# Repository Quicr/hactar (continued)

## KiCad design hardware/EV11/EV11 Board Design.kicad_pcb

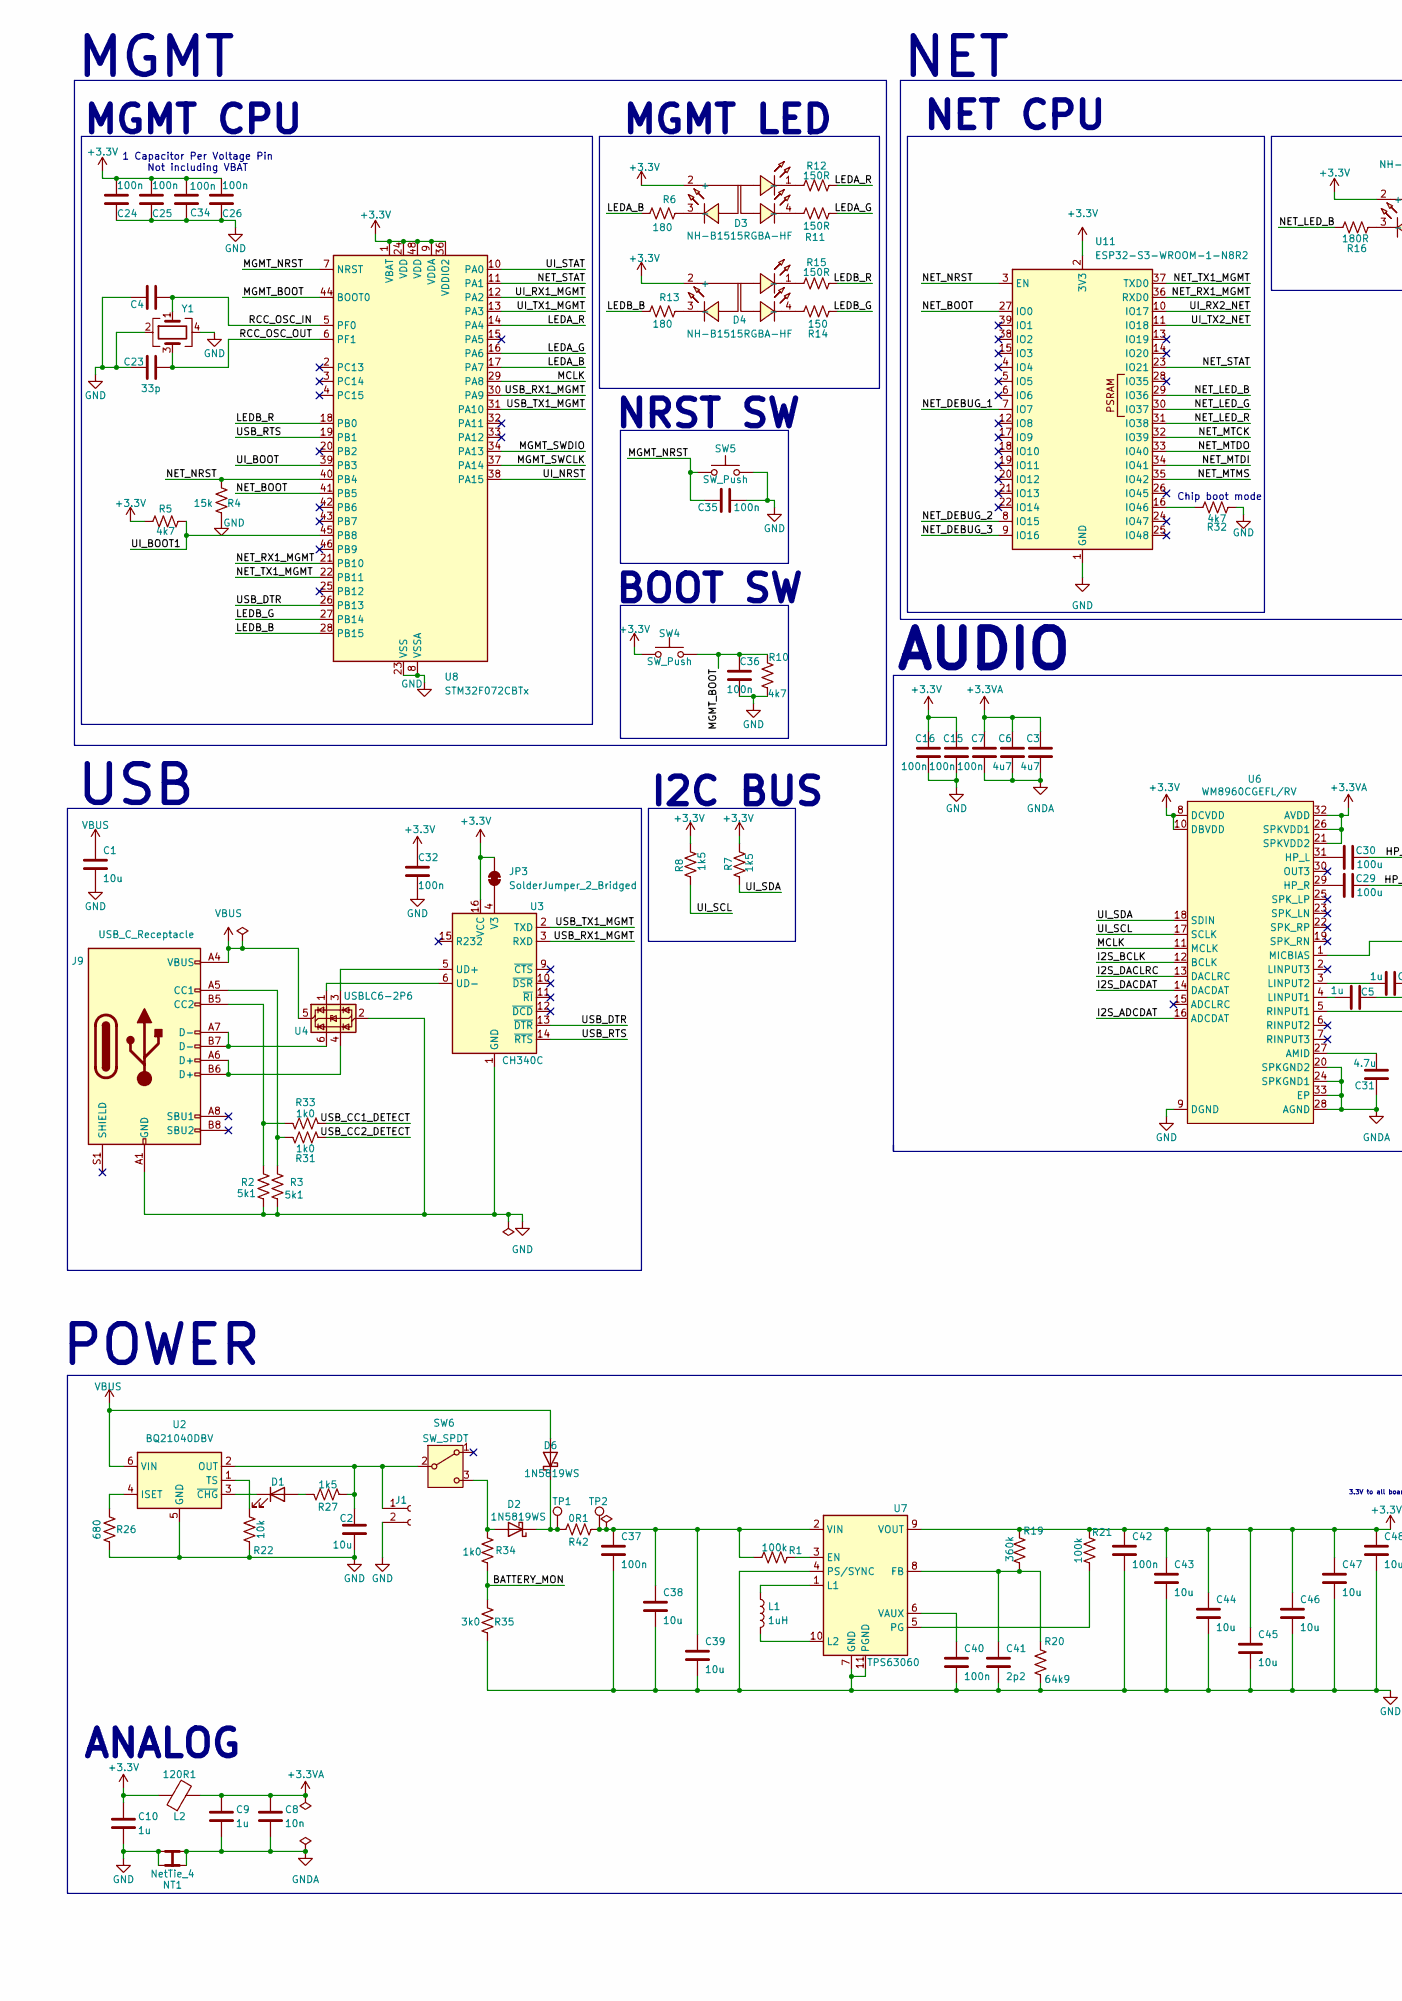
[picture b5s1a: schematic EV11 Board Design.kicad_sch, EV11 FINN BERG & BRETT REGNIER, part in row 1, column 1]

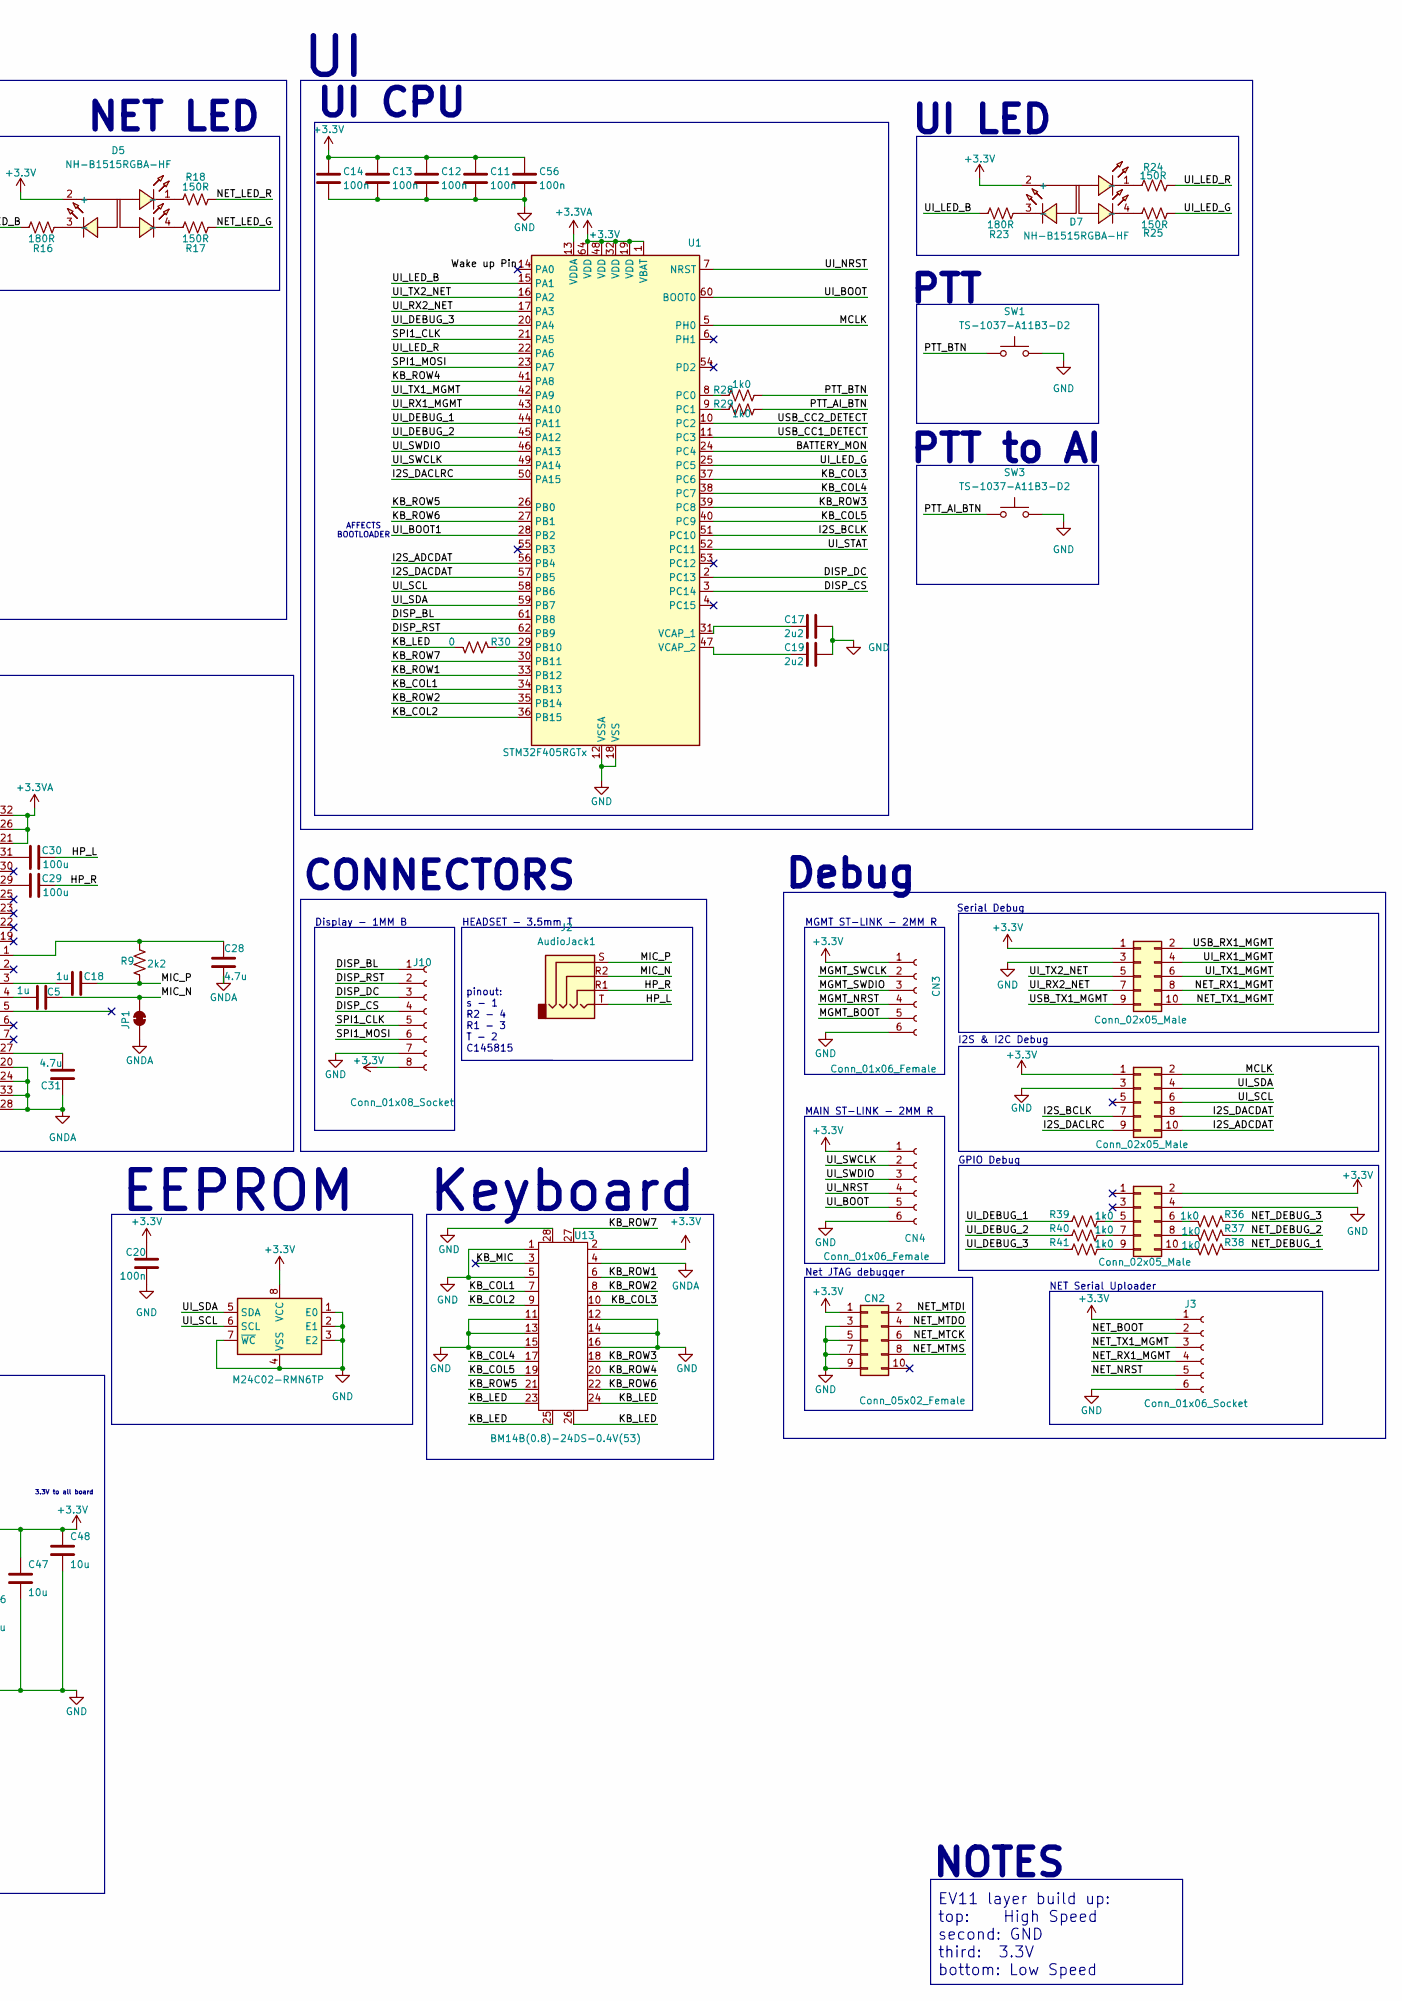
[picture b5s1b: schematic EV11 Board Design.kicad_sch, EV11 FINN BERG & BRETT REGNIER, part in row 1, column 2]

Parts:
C1, C2: 10u; C_0402_1005Metric; JLCPCB Part # C307415
C3, C6: 4u7; C_0402_1005Metric; JLCPCB Part # C23733
C4, C23: 33p; C_0805_2012Metric; JLCPCB Part # C107115
C5, C9, C10, C18: 1u; C_0402_1005Metric; JLCPCB Part # C52923
C7, C11, C12, C13, C14, C15, C16, C20, C24, C25, C26, C32, C34, C35, C36, C56: 100n; C_0402_1005Metric; JLCPCB Part # C1525
C8: 10n; C_0402_1005Metric; JLCPCB Part # C15195
C17, C19: 2u2; C_0402_1005Metric; JLCPCB Part # C12530
C28, C31: 4.7u; C_0402_1005Metric; JLCPCB Part # C23733
C29, C30: 100u; C_1206_3216Metric; JLCPCB Part # C15008
C37, C40, C42: 100n; C_0805_2012Metric; JLCPCB Part # C495959
C38, C39, C43, C44, C45, C46, C47, C48: 10u; C_0805_2012Metric; JLCPCB Part # C83061
C41: 2p2; C_0805_2012Metric; JLCPCB Part # C519933
CN2: Conn_05x02_Female; IDC-SMD_10P-P1.27_X1270WVS-2X05B-6TV01; JLCPCB Part # C2962219
CN3, CN4: Conn_01x06_Female; JST_SH_BM06B-SRSS-TB_1x06-1MP_P1.00mm_Vertical; JLCPCB Part # C3029336
CN5, CN6, CN7: Conn_02x05_Male; IDC-SMD_10P-P1.27_X1270WVS-2X05B-6TV01; JLCPCB Part # C2962219
D1: LED; D_0805_2012Metric; JLCPCB Part # C130114
D2, D6: 1N5819WS; D_SOD-323; JLCPCB Part # C191023
D3, D4, D5, D7: NH-B1515RGBA-HF; LED-ARRAY-SMD_4P-L1.6-W1.5-TL_NH-B1515RGBA; JLCPCB Part # C2874115
J1: Conn_01x02_Socket; JST_PH_S2B-PH-SM4-TB_1x02-1MP_P2.00mm_Horizontal; JLCPCB Part # C295747
J2: AudioJack1; Jack_3.5mm_PJ320D_Horizontal; MPN PJ-320D; JLCPCB Part # C431535
J3: Conn_01x06_Socket; JST_SH_BM06B-SRSS-TB_1x06-1MP_P1.00mm_Vertical; JLCPCB Part # C3029336
J9: USB_C_Receptacle; USB_C_Receptacle_HRO_TYPE-C-31-M-12; JLCPCB Part # C165948
J10: Conn_01x08_Socket; JST_SHL_SM08B-SHLS-TF_1x08-1MP_P1.00mm_Horizontal; JLCPCB Part # C3029347
JP1: SolderJumper_2_Bridged; NetTie-2_SMD_Pad0.5mm
JP3: SolderJumper_2_Bridged; SolderJumper-2_P1.3mm_Bridged_RoundedPad1.0x1.5mm
L1: 1uH; MCL2016A1R0MT; JLCPCB Part # C370013
L2: 120R1; L_0603_1608Metric; JLCPCB Part # C127301
NT1: NetTie_4; NetTie-4_SMD_Pad0.5mm
R1, R21: 100k; R_0402_1005Metric; JLCPCB Part # C25741
R2, R3: 5k1; R_0402_1005Metric; JLCPCB Part # C25905
R4: 15k; R_0402_1005Metric; JLCPCB Part # C25756
R5, R10, R32: 4k7; R_0402_1005Metric; JLCPCB Part # C25900
R6, R13: 180; R_0402_1005Metric; JLCPCB Part # C25087
R7, R8, R27: 1k5; R_0402_1005Metric; JLCPCB Part # C25867
R9: 2k2; R_0402_1005Metric; JLCPCB Part # C25879
R11, R12, R15, R17, R18, R24, R25: 150R; R_0402_1005Metric; JLCPCB Part # C25082
R14: 150; R_0402_1005Metric; JLCPCB Part # C25082
R16, R23: 180R; R_0402_1005Metric; JLCPCB Part # C25087
R19: 360k; R_0402_1005Metric; JLCPCB Part # C45956
R20: 64k9; R_0402_1005Metric; JLCPCB Part # C26984
R22: 10k; R_0402_1005Metric; JLCPCB Part # C25744
R26: 680; R_0402_1005Metric; JLCPCB Part # C25130
R28, R29, R31, R33, R34, R36, R37, R38, R39, R40, R41: 1k0; R_0402_1005Metric; JLCPCB Part # C11702
R30: 0; R_0402_1005Metric; JLCPCB Part # C17168
R35: 3k0; R_0402_1005Metric; JLCPCB Part # C25784
R42: 0R1; R_0603_1608Metric
SW1, SW3: TS-1037-A11B3-D2; KEY-SMD_2P-L7.1-W10.6-P4.00-LS9.0; JLCPCB Part # C499331
SW4, SW5: SW_Push; SW_DIP_SPSTx01_Slide_6.7x4.1mm_W6.73mm_P2.54mm_LowProfile_J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; JLCPCB Part # C266189
SW6: SW_SPDT; SW-TH_SS-12D11G5R; JLCPCB Part # C388633
TP1, TP2: TestPoint; TestPoint_THTPad_D1.5mm_Drill0.7mm
U1: STM32F405RGTx; LQFP-64_10x10mm_P0.5mm; JLCPCB Part # C15742
U2: BQ21040DBV; SOT-23-6
U3: CH340C; SOIC-16_3.9x9.9mm_P1.27mm; JLCPCB Part # C84681
U4: USBLC6-2P6; SOT-666; JLCPCB Part # C2827693
U5: M24C02-RMN6TP; SOIC-8_3.9x4.9mm_P1.27mm; JLCPCB Part # C83836
U6: WM8960CGEFL/RV; QFN-32-1EP_5x5mm_P0.5mm_EP3.45x3.45mm_ThermalVias; JLCPCB Part # C18752
U7: TPS63060; Texas_S-PWSON-N10_ThermalVias; JLCPCB Part # C48567
U8: STM32F072CBTx; LQFP-48_7x7mm_P0.5mm; JLCPCB Part # C80488
U11: ESP32-S3-WROOM-1-N8R2; ESP32-S3-WROOM-1U; JLCPCB Part # C3013944
U13: BM14B(0.8)-24DS-0.4V(53); BM14B(0.B)-24DS-0.4V(53); JLCPCB Part # C9900001863
Y1: Crystal_GND24; Crystal_SMD_3225-4Pin_3.2x2.5mm; JLCPCB Part # C13738

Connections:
+3.3V: C10.1, C11.1, C12.1, C13.1, C14.1, C15.2, C16.2, C20.2, C24.2, C25.2, C26.2, C32.1, C34.2, C42.1, C43.1, C44.1, C45.1, C46.1, C47.1, C48.1, C56.1, CN2.1, CN3.1, CN4.1, CN5.1, CN6.1, CN7.2, D3.2 (+), D4.2 (+), D5.2 (+), D7.2 (+), J3.1, J10.8, JP3.2 (B), L2.1, R5.1, R7.1, R8.1, R19.2, R21.2, SW4.1, U1.1 (VBAT), U1.19 (VDD), U1.32 (VDD), U1.48 (VDD), U1.64 (VDD), U3.16 (VCC), U5.8 (VCC), U6.8 (DCVDD), U6.10 (DBVDD), U7.9 (VOUT), U8.1 (VBAT), U8.9 (VDDA), U8.24 (VDD), U8.36 (VDDIO2), U8.48 (VDD), U11.2 (3V3), U13.2
+3.3VA: C3.1, C6.1, C7.2, C8.1, C9.1, L2.2, U1.13 (VDDA), U6.21 (SPKVDD2), U6.26 (SPKVDD1), U6.32 (AVDD)
/BATTERY_MON: R34.1, R35.2, U1.24 (PC4)
/DISP_BL: J10.1, U1.61 (PB8)
/DISP_CS: J10.4, U1.3 (PC14)
/DISP_DC: J10.3, U1.2 (PC13)
/DISP_RST: J10.2, U1.62 (PB9)
/HP_L: C30.2, J2.T
/HP_R: C29.2, J2.R1
/I2S_ADCDAT: CN5.10, U1.56 (PB4), U6.16 (ADCDAT)
/I2S_BCLK: CN5.7, U1.51 (PC10), U6.12 (BCLK)
/I2S_DACDAT: CN5.8, U1.57 (PB5), U6.14 (DACDAT)
/I2S_DACLRC: CN5.9, U1.50 (PA15), U6.13 (DACLRC)
/KB_COL1: U1.34 (PB13), U13.7
/KB_COL2: U1.36 (PB15), U13.9
/KB_COL3: U1.37 (PC6), U13.10
/KB_COL4: U1.38 (PC7), U13.17
/KB_COL5: U1.40 (PC9), U13.19
/KB_LED: R30.2, U13.23, U13.24, U13.25, U13.26
/KB_MIC: U13.3
/KB_ROW1: U1.33 (PB12), U13.6
/KB_ROW2: U1.35 (PB14), U13.8
/KB_ROW3: U1.39 (PC8), U13.18
/KB_ROW4: U1.41 (PA8), U13.20
/KB_ROW5: U1.26 (PB0), U13.21
/KB_ROW6: U1.27 (PB1), U13.22
/KB_ROW7: U1.30 (PB11), U13.27
/LEDA_B: R6.2, U8.17 (PA7)
/LEDA_G: R11.2, U8.16 (PA6)
/LEDA_R: R12.2, U8.14 (PA4)
/LEDB_B: R13.2, U8.28 (PB15)
/LEDB_G: R14.2, U8.27 (PB14)
/LEDB_R: R15.2, U8.18 (PB0)
/MCLK: CN5.2, U1.5 (PH0), U6.11 (MCLK), U8.29 (PA8)
/MGMT_BOOT: C36.2, CN3.5, R10.2, SW4.2, U8.44 (BOOT0)
/MGMT_NRST: C35.1, CN3.4, SW5.2, U8.7 (NRST)
/MGMT_SWCLK: CN3.2, U8.37 (PA14)
/MGMT_SWDIO: CN3.3, U8.34 (PA13)
/MIC_N: C5.2, J2.R2, JP1.1 (A)
/MIC_P: C18.2, J2.S, R9.1
/NET_BOOT: J3.2, U8.41 (PB5), U11.27 (IO0)
/NET_DEBUG_1: R38.1, U11.7 (IO7)
/NET_DEBUG_2: R37.1, U11.8 (IO15)
/NET_DEBUG_3: R36.1, U11.9 (IO16)
/NET_LED_B: R16.1, U11.29 (IO36)
/NET_LED_G: R17.1, U11.30 (IO37)
/NET_LED_R: R18.1, U11.31 (IO38)
/NET_MTCK: CN2.6, U11.32 (IO39)
/NET_MTDI: CN2.2, U11.34 (IO41)
/NET_MTDO: CN2.4, U11.33 (IO40)
/NET_MTMS: CN2.8, U11.35 (IO42)
/NET_NRST: J3.5, R4.1, U8.40 (PB4), U11.3 (EN)
/NET_RX1_MGMT: CN6.8, J3.4, U8.21 (PB10), U11.36 (RXD0)
/NET_STAT: U8.11 (PA1), U11.23 (IO21)
/NET_TX1_MGMT: CN6.10, J3.3, U8.22 (PB11), U11.37 (TXD0)
/PTT_AI_BTN: R29.2, SW3.1
/PTT_BTN: R28.2, SW1.1
/RCC_OSC_IN: C4.2, U8.5 (PF0), Y1.1
/RCC_OSC_OUT: C23.2, U8.6 (PF1), Y1.3
/SPI1_CLK: J10.5, U1.21 (PA5)
/SPI1_MOSI: J10.6, U1.23 (PA7)
/UI_BOOT: CN4.5, U1.60 (BOOT0), U8.39 (PB3)
/UI_BOOT1: R5.2, U1.28 (PB2), U8.45 (PB8)
/UI_DEBUG_1: R39.1, U1.44 (PA11)
/UI_DEBUG_2: R40.1, U1.45 (PA12)
/UI_DEBUG_3: R41.1, U1.20 (PA4)
/UI_LED_B: R23.1, U1.15 (PA1)
/UI_LED_G: R25.1, U1.25 (PC5)
/UI_LED_R: R24.1, U1.22 (PA6)
/UI_NRST: CN4.4, U1.7 (NRST), U8.38 (PA15)
/UI_RX1_MGMT: CN6.4, U1.43 (PA10), U8.12 (PA2)
/UI_RX2_NET: CN6.7, U1.17 (PA3), U11.10 (IO17)
/UI_SCL: CN5.6, R8.2, U1.58 (PB6), U5.6 (SCL), U6.17 (SCLK)
/UI_SDA: CN5.4, R7.2, U1.59 (PB7), U5.5 (SDA), U6.18 (SDIN)
/UI_STAT: U1.52 (PC11), U8.10 (PA0)
/UI_SWCLK: CN4.2, U1.49 (PA14)
/UI_SWDIO: CN4.3, U1.46 (PA13)
/UI_TX1_MGMT: CN6.6, U1.42 (PA9), U8.13 (PA3)
/UI_TX2_NET: CN6.5, U1.16 (PA2), U11.11 (IO18)
/USB_CC1_DETECT: R33.1, U1.11 (PC3)
/USB_CC2_DETECT: R31.1, U1.10 (PC2)
/USB_DTR: U3.13 (~DTR), U8.26 (PB13)
/USB_RTS: U3.14 (~RTS), U8.19 (PB1)
/USB_RX1_MGMT: CN6.2, U3.3 (RXD), U8.30 (PA9)
/USB_TX1_MGMT: CN6.9, U3.2 (TXD), U8.31 (PA10)
/Wake up Pin: U1.14 (PA0)
GND: C1.2, C2.2, C4.1, C10.2, C11.2, C12.2, C13.2, C14.2, C15.1, C16.1, C17.1, C19.1, C20.1, C23.1, C24.1, C25.1, C26.1, C32.2, C34.1, C35.2, C36.1, C37.2, C38.2, C39.2, C40.2, C41.2, C42.2, C43.2, C44.2, C45.2, C46.2, C47.2, C48.2, C56.2, CN2.3, CN2.5, CN2.7, CN2.9, CN3.6, CN4.6, CN5.3, CN6.3, CN7.4, J1.2, J3.6, J9.A1 (GND), J9.A12 (GND), J9.B1 (GND), J9.B12 (GND), J10.7, NT1.1, NT1.3, R2.1, R3.1, R4.2, R10.1, R20.1, R22.2, R26.2, R32.2, R35.1, SW1.2, SW3.2, SW5.1, U1.12 (VSSA), U1.18 (VSS), U1.63 (VSS), U2.5 (GND), U3.1 (GND), U4.2 (GND), U5.1 (E0), U5.2 (E1), U5.3 (E2), U5.4 (VSS), U5.7 (~WC), U6.9 (DGND), U7.4 (PS/SYNC), U7.7 (GND), U7.11 (PGND), U8.8 (VSSA), U8.23 (VSS), U8.35 (VSS), U8.47 (VSS), U11.1 (GND), U11.40 (GND), U11.41 (GND), U13.1, U13.5, U13.11, U13.12, U13.13, U13.14, U13.15, U13.16, U13.28, Y1.2, Y1.4
GNDA: C3.2, C6.2, C7.1, C8.2, C9.2, C28.2, C31.2, JP1.2 (B), NT1.2, NT1.4, U6.20 (SPKGND2), U6.24 (SPKGND1), U6.28 (AGND), U6.33 (EP), U13.4
unnamed: CN7.5, R39.2
unnamed: CN7.6, R36.2
unnamed: CN7.7, R40.2
unnamed: CN7.8, R37.2
unnamed: CN7.9, R41.2
unnamed: CN7.10, R38.2
unnamed: D1.2 (A), R27.2
unnamed: D1.1 (K), U2.3 (~CHG)
unnamed: D2.2 (A), R34.2, SW6.3 (C)
unnamed: D2.1 (K), D6.1 (K), R42.1, TP1.1
unnamed: D3.1 (-), R12.1
unnamed: D3.3 (-), R6.1
unnamed: D3.4 (-), R11.1
unnamed: D4.1 (-), R15.1
unnamed: D4.3 (-), R13.1
unnamed: D4.4 (-), R14.1
unnamed: D5.1 (-), R18.2
unnamed: D5.3 (-), R16.2
unnamed: D5.4 (-), R17.2
unnamed: D7.1 (-), R24.2
unnamed: D7.3 (-), R23.2
unnamed: D7.4 (-), R25.2
unnamed: C2.1, J1.1, R27.1, SW6.2 (B), U2.2 (OUT)
unnamed: J9.A5 (CC1), R3.2, R31.2
unnamed: J9.B5 (CC2), R2.2, R33.2
unnamed: J9.A6 (D+), J9.B6 (D+), U4.4 (I/O2)
unnamed: J9.A7 (D-), J9.B7 (D-), U4.6 (I/O1)
unnamed: JP3.1 (A), U3.4 (V3)
unnamed: R30.1, U1.29 (PB10)
unnamed: R28.1, U1.8 (PC0)
unnamed: R29.1, U1.9 (PC1)
unnamed: C17.2, U1.31 (VCAP_1)
unnamed: C19.2, U1.47 (VCAP_2)
unnamed: R26.1, U2.4 (ISET)
unnamed: R22.1, U2.1 (TS)
unnamed: U3.5 (UD+), U4.3 (I/O2)
unnamed: U3.6 (UD-), U4.1 (I/O1)
unnamed: C31.1, U6.27 (AMID)
unnamed: C30.1, U6.31 (HP_L)
unnamed: C29.1, U6.29 (HP_R)
unnamed: C5.1, U6.4 (LINPUT1)
unnamed: C18.1, U6.3 (LINPUT2)
unnamed: C28.1, R9.2, U6.1 (MICBIAS)
unnamed: R1.2, U7.3 (EN)
unnamed: C41.1, R19.1, R20.2, U7.8 (FB)
unnamed: L1.1, U7.1 (L1)
unnamed: L1.2, U7.10 (L2)
unnamed: R21.1, U7.5 (PG)
unnamed: C40.1, U7.6 (VAUX)
unnamed: C37.1, C38.1, C39.1, R1.1, R42.2, TP2.1, U7.2 (VIN)
unnamed: R32.1, U11.16 (IO46)
VBUS: C1.1, D6.2 (A), J9.A4 (VBUS), J9.A9 (VBUS), J9.B4 (VBUS), J9.B9 (VBUS), U2.6 (VIN), U4.5 (VBUS)

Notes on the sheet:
MGMT
NET CPU
pinout: s - 1 R2 - 4 R1 - 3 T - 2 C145815
Serial Debug
MGMT CPU
PTT to AI
NET
POWER
AFFECTS BOOTLOADER
CONNECTORS
NET LED
UI CPU
MAIN ST-LINK - 2MM R
HEADSET - 3.5mm T
Chip boot mode
Net JTAG debugger
NET Serial Uploader
NRST SW
EV11 layer build up: top: High Speed second: GND third: 3.3V bottom: Low Speed
Debug
AUDIO
PTT
BOOT SW
EEPROM
I2C BUS
MGMT ST-LINK - 2MM R
USB
MGMT LED
3.3V to all board
NOTES
Keyboard
Display - 1MM B
I2S & I2C Debug
GPIO Debug
1 Capacitor Per Voltage Pin Not including VBAT
UI LED
ANALOG

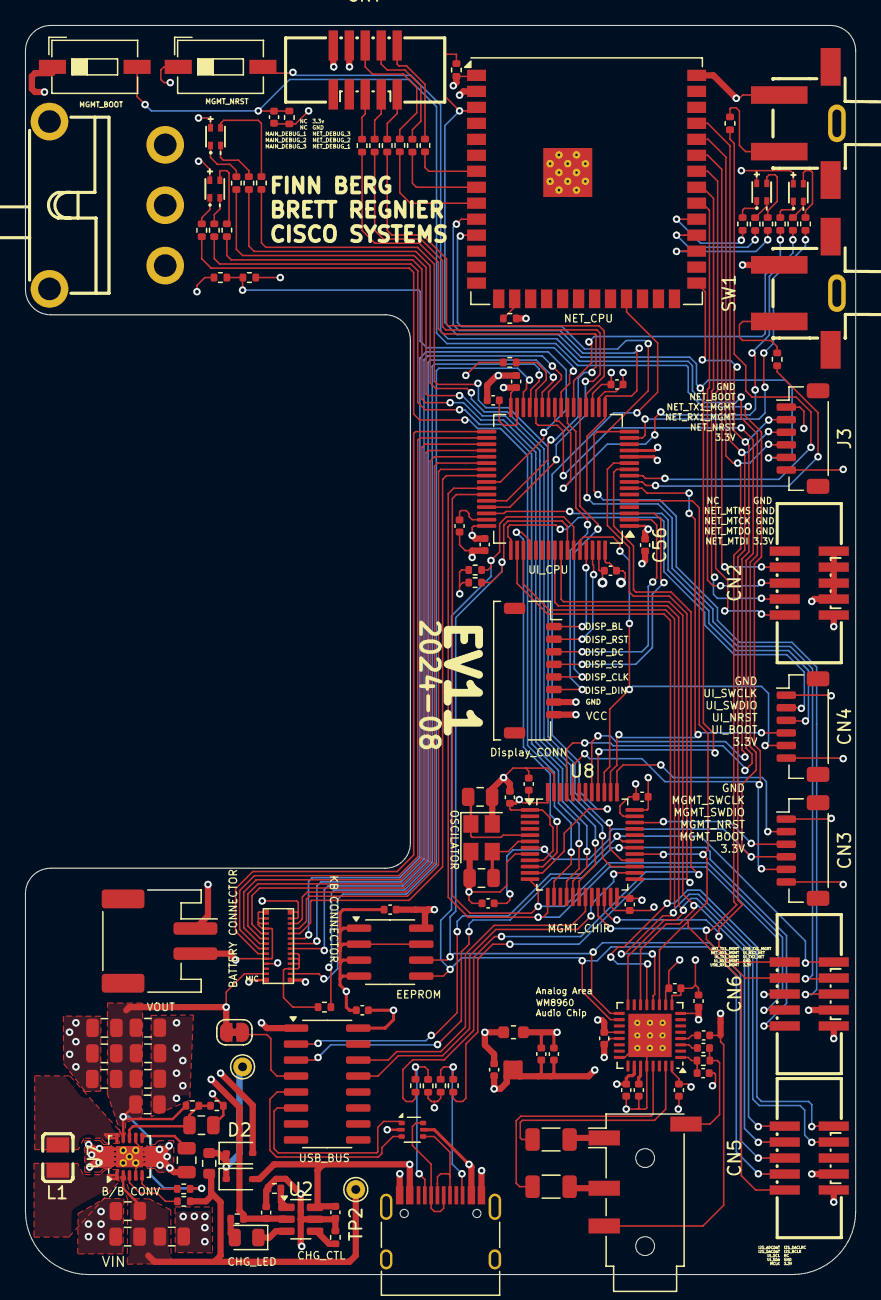
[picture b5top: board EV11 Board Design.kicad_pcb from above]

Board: 4 copper layers, 66.0 x 99.3 mm, 128 parts (0 on the bottom side), 138 nets.

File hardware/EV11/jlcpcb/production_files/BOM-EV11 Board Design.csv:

Comment,Designator,Footprint,LCSC
33P,"C23,C4",C_0805_2012Metric,C107115
2u2,"C21,C22",C_0402_1005Metric,C12530
FerriteBead,120R1,L_0603_1608Metric,C127301
Crystal_GND24,Y1,Crystal_SMD_3225-4Pin_3.2x2.5mm,C13738
100U,"C29,C30",C_1206_3216Metric,C15008
10n,C8,C_0402_1005Metric,C15195
100n,"C11,C12,C13,C14,C15,C16,C24,C25,C26,C32,C33,C34,C35,C36,C7",C_0402_1005Metric,C1525
STM32F405RGTx,U1,LQFP-64_10x10mm_P0.5mm,C15742
USB_C_Receptacle,J9,USB_C_Receptacle_HRO_TYPE-C-31-M-12,C165948
0,R41,R_0402_1005Metric,C17168
WM8960CGEFL/RV,U6,QFN50P500X500X90-33N,C18752
4.7u,"C28,C3,C31,C6",C_0402_1005Metric,C23733
150,"R11,R12,R14,R15,R17,R18,R24,R25",R_0402_1005Metric,C25082
180,"R13,R16,R23,R6",R_0402_1005Metric,C25087
15k,R4,R_0402_1005Metric,C25756
1k5,"R7,R8",R_0402_1005Metric,C25867
2K2,R9,R_0402_1005Metric,C25879
4k7,"R10,R32,R5",R_0402_1005Metric,C25900
5k1,"R2,R3",R_0402_1005Metric,C25905
Conn_01x06_Female,J11,JST_PH_S6B-PH-SM4-TB_1x06-1MP_P2.00mm_Horizontal,C265405
SW_Push,"SW4,SW5",SW_DIP_SPSTx01_Slide_6.7x4.1mm_W6.73mm_P2.54mm_LowProfile_JPin,C266189
USBLC6-2P6,U4,SOT-666,C2827693
ASMB-MTB1-0A3A2,"D18,D3,D4,D5",LED RGB,C2874115
ESP32-S3-WROOM-1-N8R2,U11,ESP32-S3-WROOM-1U,C3013944
Conn_01x04_Female,"J13,J7",1x4pin 1mm connector,C3029343
1u,"C10,C17,C18,C9",C_0402_1005Metric,C52923
STM32F030C8Tx,U5,LQFP-48_7x7mm_P0.5mm,C80488
M24C02-RDW6TP,CR1,New_ESP32_M24C02-RMN6TP,C83836
CH340C,U3,SOIC-16_3.9x9.9mm_P1.27mm,C84681
10u,C45,C_0805_2012Metric,
10u,C1,C_0402_1005Metric,
0.1u,C40,C_0805_2012Metric,
10u,C39,C_0805_2012Metric,
100k,R1,R_0402_1005Metric,
AudioPlug4,J4,PJ_313E_8A,
10u,C38,C_0805_2012Metric,
64.9k,R20,R_0402_1005Metric,
0.1u,C42,C_0805_2012Metric,
Conn_01x08_Socket,J10,JST_SHL_SM08B-SHLS-TF_1x08-1MP_P1.00mm_Horizontal,
BM14B(0.8)-24DS-0.4V(53),U13,BM14B(0.B)-24DS-0.4V(53),
Conn_01x02_Socket,J1,JST_PH_S2B-PH-SM4-TB_1x02-1MP_P2.00mm_Horizontal,
LED,D1,D_0805_2012Metric,
10u,C48,C_0805_2012Metric,
BQ21040DBVR,U2,SOT95P280X145-6N,
10k,R22,R_0402_1005Metric,
360k,R19,R_0402_1005Metric,
10u,C46,C_0805_2012Metric,
1k5,R27,R_0402_1005Metric,
100k,R21,R_0402_1005Metric,
1N5819WS,D2,D_SOD-323,
1uH,L1,L_0805_2012Metric,
1N5819WS,D6,D_SOD-323,
10u,C2,C_0402_1005Metric,
2.2p,C41,C_0805_2012Metric,
680,R26,R_0402_1005Metric,
10u,C43,C_0805_2012Metric,
Conn_01x02_Socket,J5,JST_PH_S2B-PH-SM4-TB_1x02-1MP_P2.00mm_Horizontal,
0.1u,C37,C_0805_2012Metric,
TPS63060,U7,Texas_S-PWSON-N10_ThermalVias,
10u,C47,C_0805_2012Metric,
10u,C44,C_0805_2012Metric,
